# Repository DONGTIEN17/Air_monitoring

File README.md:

# Air Monitoring System

## Problem Statement
### Real-World Demand

With rapid urbanization, air pollution has become a critical issue directly affecting public health—especially in densely populated cities like Ha Noi, where smog, vehicle emissions, and industrial activities frequently push air quality to hazardous levels. Traditional air-monitoring methods often fall short, providing delayed or incomplete information. This reality highlights the urgent need for a smart air-monitoring system capable of:

Multi-Parameter Monitoring: Continuously measuring essential environmental indicators such as PM2.5, temperature, humidity, pressure, and VOC levels.

Enhanced Safety Alerts: Automatically detecting dangerous conditions—high pollution peaks, toxic gas leaks, or abnormal temperature changes—and warning users in real time.

Automation and Accessibility: Offering a low-cost, easy-to-deploy solution that brings advanced environmental monitoring to households, schools, offices, and communities.

### Inspiration for the Project

Toxic Gas Incidents: Urban areas have seen rising risks of gas leaks and poor air quality, demonstrating the importance of real-time automated alerts to protect residents.

Data Accuracy Challenges: Many existing monitoring tools suffer from unstable readings and slow updates. This project emphasizes the use of reliable sensors and intuitive interfaces to provide accurate, timely information for better decision-making.

## Main Content
### Hardware Components
#### Hardware List
Component	Quantity	Function :

_ESP32 DevKit	Central processing, control, and network connectivity.

_BME680 Environmental Sensor	1	Measures Temperature, Humidity, Pressure, and VOC/Gas Index.

_ PMS5003 Dust Sensor	1	Monitors PM1, PM2.5, PM10 concentrations.

_GPS Module (NEO-6M / ATGM336H)	1	Provides GPS coordinates (Latitude, Longitude, Satellite count).

_OLED Display (I2C)	1	Displays real-time environmental data.

_LED Warning Indicator	1	Alerts when air quality thresholds are exceeded.

_Cables + Power Source	—	For wiring and powering the system.

### Software Overview

#### Node-RED Dashboard

_Visualization: Displays real-time data for PM1, PM2.5, PM10, Temperature, Humidity, Pressure, location of monitor, AQI, IAQ .

_Management: Set alert thresholds, control system status, and monitor historical data.

_Safety Monitoring: Receive alerts for high pollution levels, toxic gases, and abnormal temperature or humidity.

#### MQTT Broker

_EMQX used for real-time data transmission.

_ESP32 publishes sensor data to the broker.

_Node-RED subscribes to this data and updates the dashboard accordingly.

_Virtual machine subcribes and publishes value

#### Development Environment

_PlatformIO with VS Code.

_Virtual Machine (VMWare or Install on your window)

_Google Colab to train model

#### System Concept

Data Collection:

_PMS5003 measures particulate matter (PM2.5, PM10).

_BME680 captures temperature, humidity, pressure, and VOC levels.

_GPS module provides location coordinates.

Local Processing:

_The ESP32 processes sensor data, checks against thresholds, and updates the OLED display.

_The LED indicator provides a visual warning when air quality falls below safe levels.

Cloud Communication:

_ESP32 sends data to the MQTT broker.

_Node-RED retrieves and visualizes this data on the dashboard.

_Virtual Machine subcribes and publishes to broker to predict the AQI

Visualization & Alerts:

_The dashboard shows real-time data and alerts for any abnormal conditions.

_Users can set thresholds and receive notifications for environmental hazards.

## AI model

To enhance the accuracy and reliability of air quality forecasting, this project employs an LSTM (Long Short-Term Memory) neural network—an advanced deep-learning model well-suited for time-series prediction. By learning from historical sensor data, the model can predict the Air Quality Index (AQI) several hours ahead, enabling earlier awareness and more proactive responses to pollution.

Below is a comparison between the actual AQI values and the model’s predicted results, demonstrating the strong alignment between the two:

And here is the model evaluation, showing the performance metrics used to validate prediction accuracy:

## Block Diagram 

1. Block Diagram

4. Algorithm Flow Chart

## Pin Diagram

3. Pin Diagram

## Result

1. Model:

3. Node-red dashboard 2.0 :

. The Node-red dashboard consists of 7 Tabs: Home, Air Quality Collected, Particulate Matter Indicators, Weather, Air Purifier, Location of Monitor, Another Web.

.The Home interface displays AQI, IAQ, Temperature and Humidity and give the thresholds alert.

. The Particulate Matter Indicators displays 3 types of PM : PM1, PM2.5, PM10 collected that time.

. The Weather displays Temperature, Humidity, Pressure readings, along with historical data over time.

. The Air Purifier to turn on/off if the air is poluted

. The Location of Monitor 

. The Another Web helps people compare the air quality index at their home with other locations.

## Conclusion
. Air Monitoring system has been successfully developed with the following features:

  Collects data from sensors

  Provides warnings to users 

  Successfully uses an AI model to predict AQI with high accuracy

  Creates a visual platform that is easy for people to use

  Includes a database suitable for various applications

. The MQTT protocol has been successfully implemented to transmit and receive data between system components via brokers like HiveMQ or EMQX.

# Video Demo
Link gg Drive : https://drive.google.com/file/d/1JtE_UMB9cyV8rW0lYHocKMN55pcUekPe/view?usp=sharing

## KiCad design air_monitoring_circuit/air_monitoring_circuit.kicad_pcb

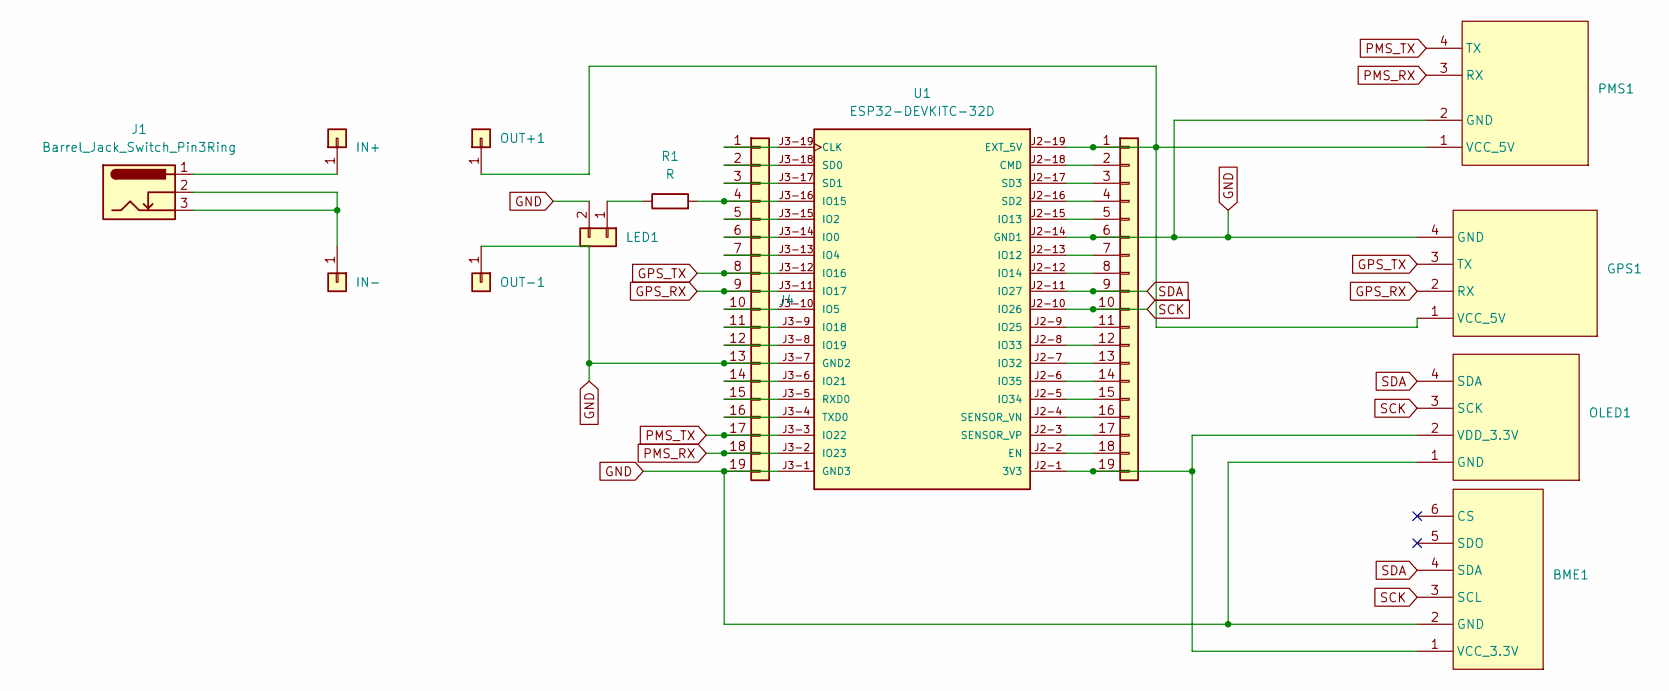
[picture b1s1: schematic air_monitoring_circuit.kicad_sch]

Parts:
BME1: PinHeader_1x06_P2.54mm_Vertical
GPS1: PinHeader_1x04_P2.54mm_Vertical
J1: Barrel_Jack_Switch_Pin3Ring; BarrelJack_Wuerth_6941xx301002
J2: IN+; PinHeader_1x01_P2.54mm_Vertical
J3: IN-; PinHeader_1x01_P2.54mm_Vertical
J4, J5: Conn_01x19; PinHeader_1x19_P2.54mm_Vertical
LED1: Conn_01x02; PinHeader_1x02_P2.54mm_Vertical
OLED1: PinHeader_1x04_P2.54mm_Vertical
OUT+1: Conn_01x01; PinHeader_1x01_P2.54mm_Vertical
OUT-1: Conn_01x01; PinHeader_1x01_P2.54mm_Vertical
PMS1: PinHeader_1x04_P2.54mm_Vertical
R1: R; R_Axial_DIN0207_L6.3mm_D2.5mm_P10.16mm_Horizontal
U1: ESP32-DEVKITC-32D; MODULE_ESP32-DEVKITC-32D; PARTREV V4

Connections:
GND: BME1.2 (GND), GPS1.4 (GND), J4.13, J4.19, J5.6, LED1.2, OLED1.1 (GND), OUT-1.1, PMS1.2 (GND), U1.J2-14 (GND1), U1.J3-1 (GND3), U1.J3-7 (GND2)
GPS_RX: GPS1.2 (RX), J4.9, U1.J3-11 (IO17)
GPS_TX: GPS1.3 (TX), J4.8, U1.J3-12 (IO16)
unnamed: BME1.1 (VCC_3.3V), J5.19, OLED1.2 (VDD_3.3V), U1.J2-1 (3V3)
unnamed: GPS1.1 (VCC_5V), J5.1, OUT+1.1, PMS1.1 (VCC_5V), U1.J2-19 (EXT_5V)
unnamed: J1.1, J2.1
unnamed: J1.2, J1.3, J3.1
unnamed: J4.1, U1.J3-19 (CLK)
unnamed: J4.2, U1.J3-18 (SD0)
unnamed: J4.3, U1.J3-17 (SD1)
unnamed: J4.4, R1.2, U1.J3-16 (IO15)
unnamed: J4.5, U1.J3-15 (IO2)
unnamed: J4.6, U1.J3-14 (IO0)
unnamed: J4.7, U1.J3-13 (IO4)
unnamed: J4.10, U1.J3-10 (IO5)
unnamed: J4.11, U1.J3-9 (IO18)
unnamed: J4.12, U1.J3-8 (IO19)
unnamed: J4.14, U1.J3-6 (IO21)
unnamed: J4.15, U1.J3-5 (RXD0)
unnamed: J4.16, U1.J3-4 (TXD0)
unnamed: J5.2, U1.J2-18 (CMD)
unnamed: J5.3, U1.J2-17 (SD3)
unnamed: J5.4, U1.J2-16 (SD2)
unnamed: J5.5, U1.J2-15 (IO13)
unnamed: J5.7, U1.J2-13 (IO12)
unnamed: J5.8, U1.J2-12 (IO14)
unnamed: J5.11, U1.J2-9 (IO25)
unnamed: J5.12, U1.J2-8 (IO33)
unnamed: J5.13, U1.J2-7 (IO32)
unnamed: J5.14, U1.J2-6 (IO35)
unnamed: J5.15, U1.J2-5 (IO34)
unnamed: J5.16, U1.J2-4 (SENSOR_VN)
unnamed: J5.17, U1.J2-3 (SENSOR_VP)
unnamed: J5.18, U1.J2-2 (EN)
unnamed: LED1.1, R1.1
PMS_RX: J4.18, PMS1.3 (RX), U1.J3-2 (IO23)
PMS_TX: J4.17, PMS1.4 (TX), U1.J3-3 (IO22)
SCK: BME1.3 (SCL), J5.10, OLED1.3 (SCK), U1.J2-10 (IO26)
SDA: BME1.4 (SDA), J5.9, OLED1.4 (SDA), U1.J2-11 (IO27)

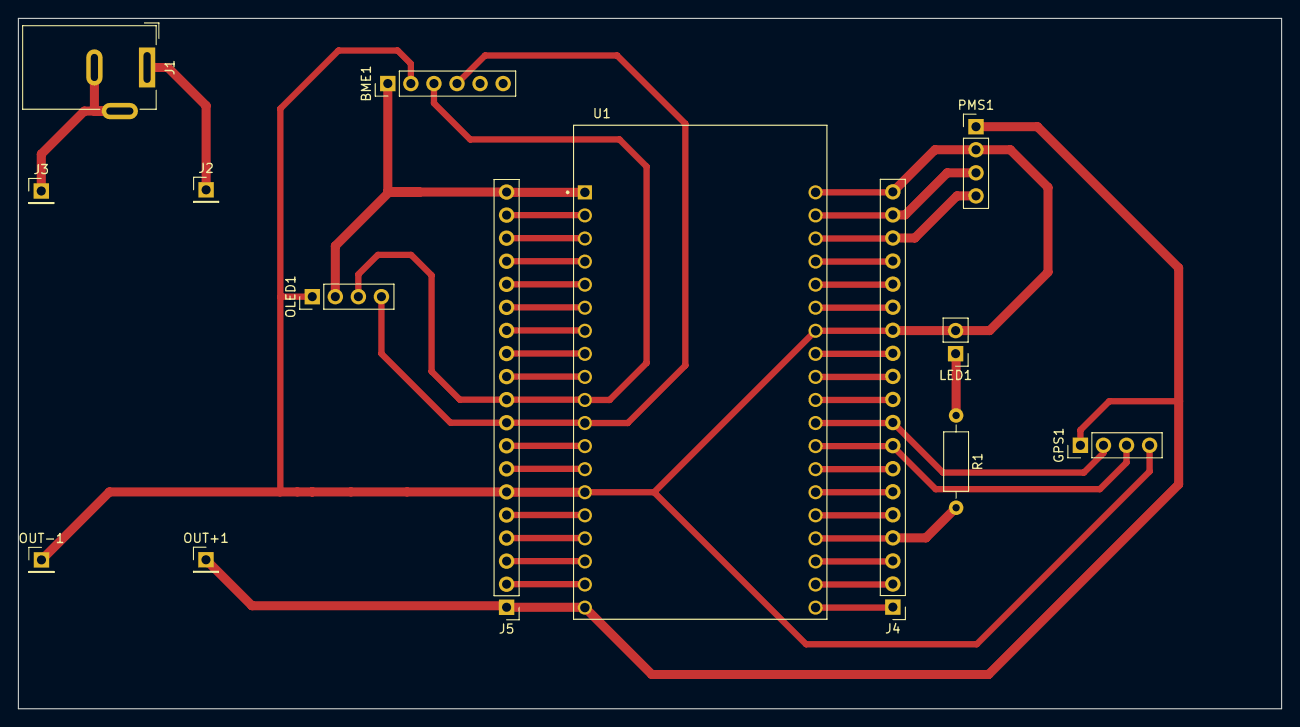
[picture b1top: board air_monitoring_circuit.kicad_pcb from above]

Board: 2 copper layers, 139.1 x 76.0 mm, 14 parts (0 on the bottom side), 39 nets.

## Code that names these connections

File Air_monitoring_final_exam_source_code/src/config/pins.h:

#pragma once

// =========================
//        PMS SENSOR
// =========================
#define PMS_TX 23
#define PMS_RX 22
// =========================
//        BME680
// =========================
#define BME_SCL 26
#define BME_SDA 27

// =========================
//        GPS MODULE
// =========================
#define GPS_TX 17
#define GPS_RX 16

// =========================
//        OLED SCREEN
// =========================
#define OLED_SCL 26
#define OLED_SDA 27
#define OLED_ADDR 0x3C
#define SCREEN_WIDTH 128
#define SCREEN_HEIGHT 64

// =========================
//      LED DEVICES
// =========================
#define LED_PIN 2          // Air filter ON/OFF
#define LED_Warning 14     // Warning LED (Blinking)

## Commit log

2025-12-11 remove ignore and add files
2025-12-11 save changes
2025-12-12 Update folder structure
